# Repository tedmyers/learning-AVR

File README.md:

# learning-AVR
Repository for simple programs for teaching the basics of AVR. 

Code was originally written for the Atmega328P microcontroller, for the Northeastern Wireless Club LED Group.

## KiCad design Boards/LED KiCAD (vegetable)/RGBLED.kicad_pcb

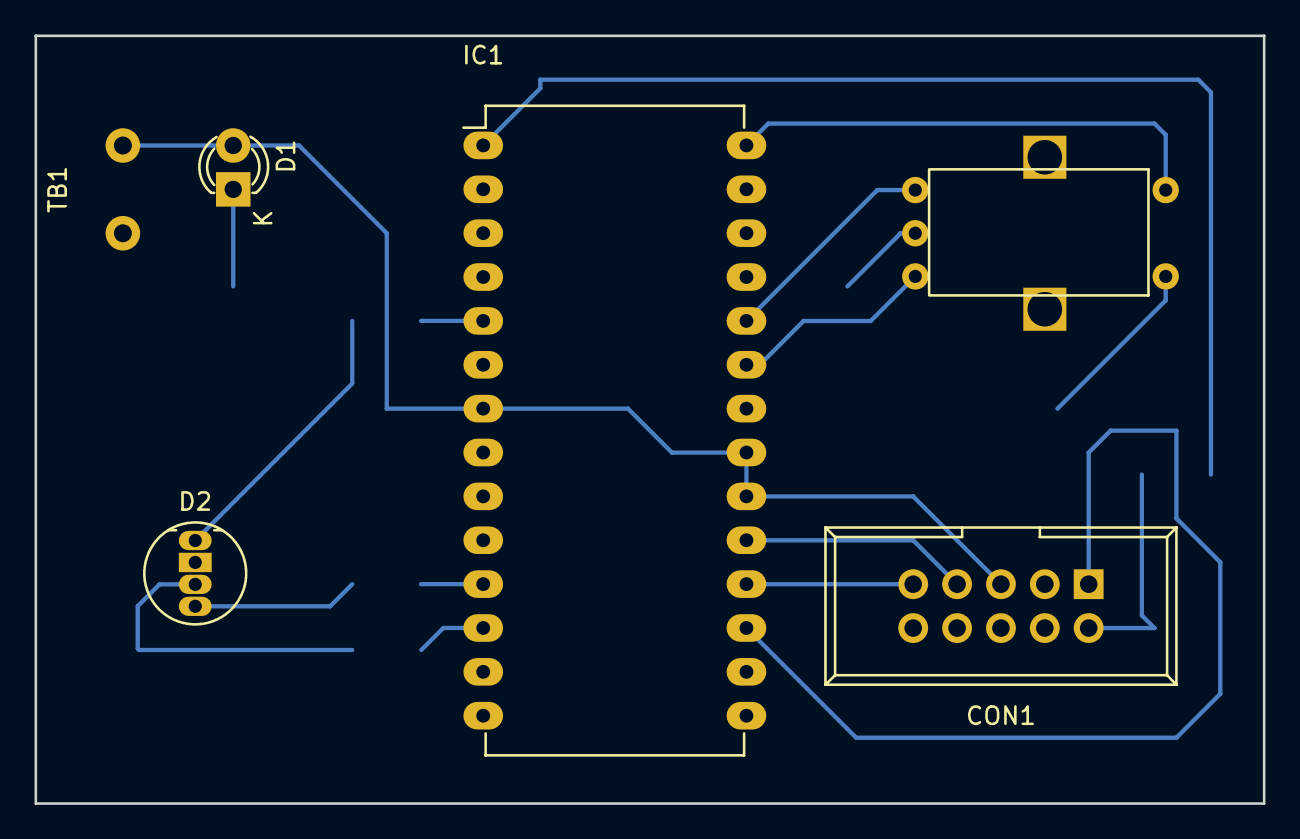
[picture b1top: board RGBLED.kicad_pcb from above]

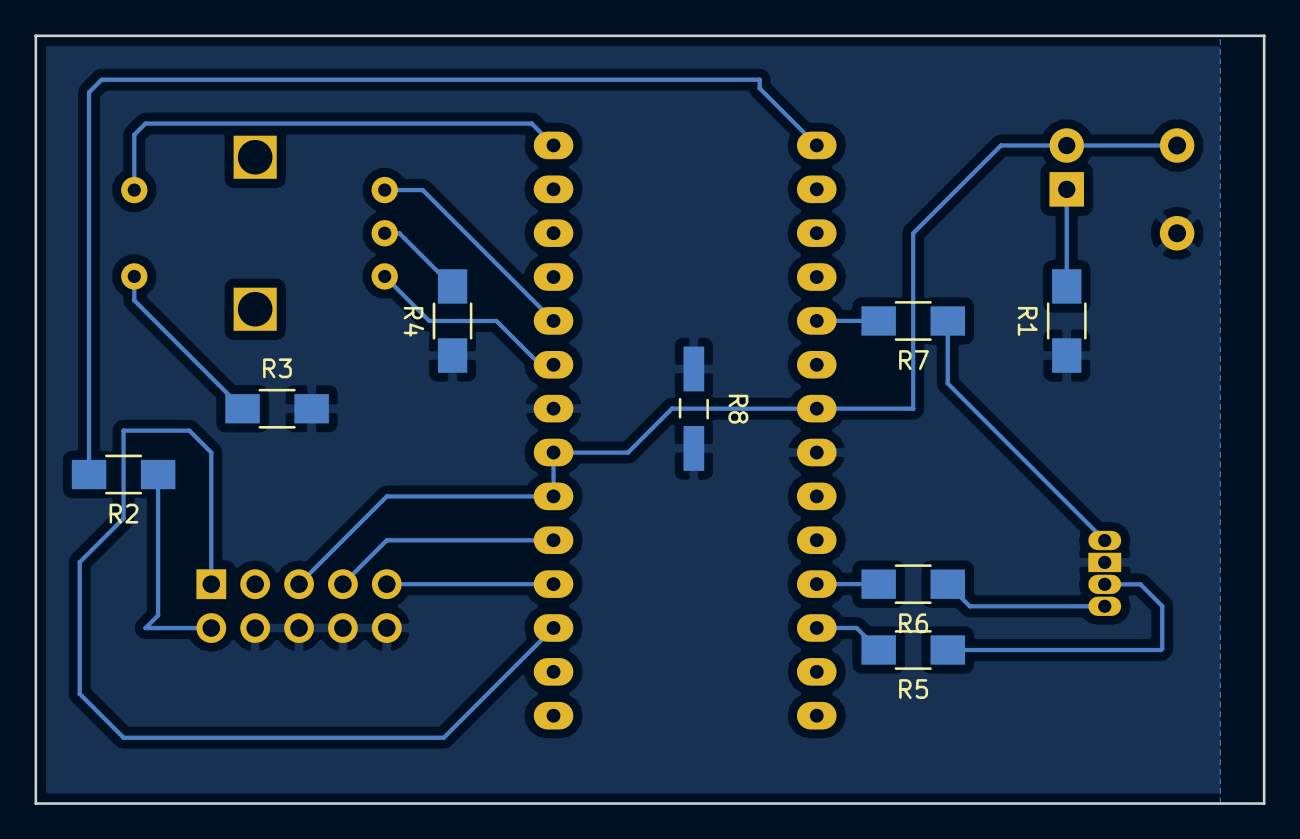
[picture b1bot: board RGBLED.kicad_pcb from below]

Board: 2 copper layers, 71.1 x 44.5 mm, 14 parts (8 on the bottom side), 18 nets.

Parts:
CON1: AVR-ISP-10; IDC_Header_Straight_10pins
D1: LED; LED-3MM
D2: LED_RCBG; LED-RGB-5MM_Common_Cathode
ENC1: Rotary_Encoder; Rotary_encoder
IC1: ATMEGA328-P; DIP-28_W15.24mm_LongPads
R1: 330; R_1206_HandSoldering
R2, R3, R4: 10k; R_1206_HandSoldering
R5: 660; R_1206_HandSoldering
R6, R7: 200; R_1206_HandSoldering
R8: 0; Choke_SMD_1206_Handsoldering
TB1: Screw_Terminal

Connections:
+5V: CON1.2, CON1.5, D1.2, IC1.7, IC1.20, IC1.21, R2.1, TB1.2
/Blue: IC1.12, R5.2
/But1: ENC1.2, IC1.28
/Green: IC1.11, R6.2
/MISO: CON1.9, IC1.18
/MOSI: CON1.1, IC1.17
/Red: IC1.5, R7.2
/Rot1_A: ENC1.4, IC1.23
/Rot1_B: ENC1.5, IC1.24
/SCK: CON1.7, IC1.19
GND: CON1.4, CON1.6, CON1.8, CON1.10, D2.2, IC1.8, IC1.22, R1.1, R3.2, R4.1, R8.1, R8.2, TB1.1
unnamed: D1.1, R1.2
unnamed: D2.1, R7.1
unnamed: D2.3, R5.1
unnamed: D2.4, R6.1
unnamed: ENC1.1, R3.1
unnamed: ENC1.3, R4.2
unnamed: IC1.1, R2.2

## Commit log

2016-03-16 Added Seth's Xcode PWM Files
    Added Xcode files created by Seth Penna
2016-03-16 Added more comments, moved pwm_init
    Added comments, mostly page numbers
    Added function prototype and moved pm_init() to after main()
2016-03-18 Labeling, gitignore
    Added pin definitions for red, green, blue, encoder, and button pins
    Added a git ignore files for the hex files
2016-03-20 Blink Program
    Added Blink Program
    Flashes each color in sequence on the LED boards
2016-03-21 Updated ReadMe
    Slightly modified readme file
2016-03-21 Added KiCad Schematics
    Added Schematics for the Vegetable Boards (LED KiCad) and Fruit Boards
    (Led KiCad 3)
2016-03-21 Added Button Project
    Added simple button project
    Note: buttons are different on fruit and vegetable boards; this is
    noted in code. Comment out or delete the non-applicable section for
    your board.
2016-03-21 Added Button.c
    Files
2016-03-22 Added Rotary Encoder
    This file includes the code to use the rotary encoder as well as the
    button attached to it. All code is commented, and works currently with
    the vegetable boards. Changing to the fruit boards will require a
    redefining of pins for the button and the interrupts associated with it.
2016-03-22 Updated
    Added line to easily change pins for different board types (fruit or
    vegetable). Also fixed some comments to more accurately reflect
    changes.
2016-03-22 Added interrupts
    This file includes code for a basic interrupt detection on the button
    for the rotary encoder. When the button is pressed one LED turns on.
    Currently the LED stays on, but this program could be improved to turn
    the LED off after a certain amount of time or with a second button
    press.
2016-03-22 Added RGB_LED_Control
    This code will control all three channels on the small prototype
    boards. By pressing the button the current channel is changed between
    the three colors, and turning the rotary encoder will change the active
    channel. Includes interrupts and PWM which were covered in previous
    codes.
2016-04-08 Re-added kicad files
2016-04-08 Changed comment
    Changed from turn all of port D to PD5
